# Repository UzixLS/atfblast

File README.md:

## ATFBlast/U

ATF16V8, GAL16V8, ATF22V10 and GAL22V10 chips programmer.

This is custom PCB variant of ATFBlast project.

See http://www.bhabbott.net.nz/atfblast.html for details.

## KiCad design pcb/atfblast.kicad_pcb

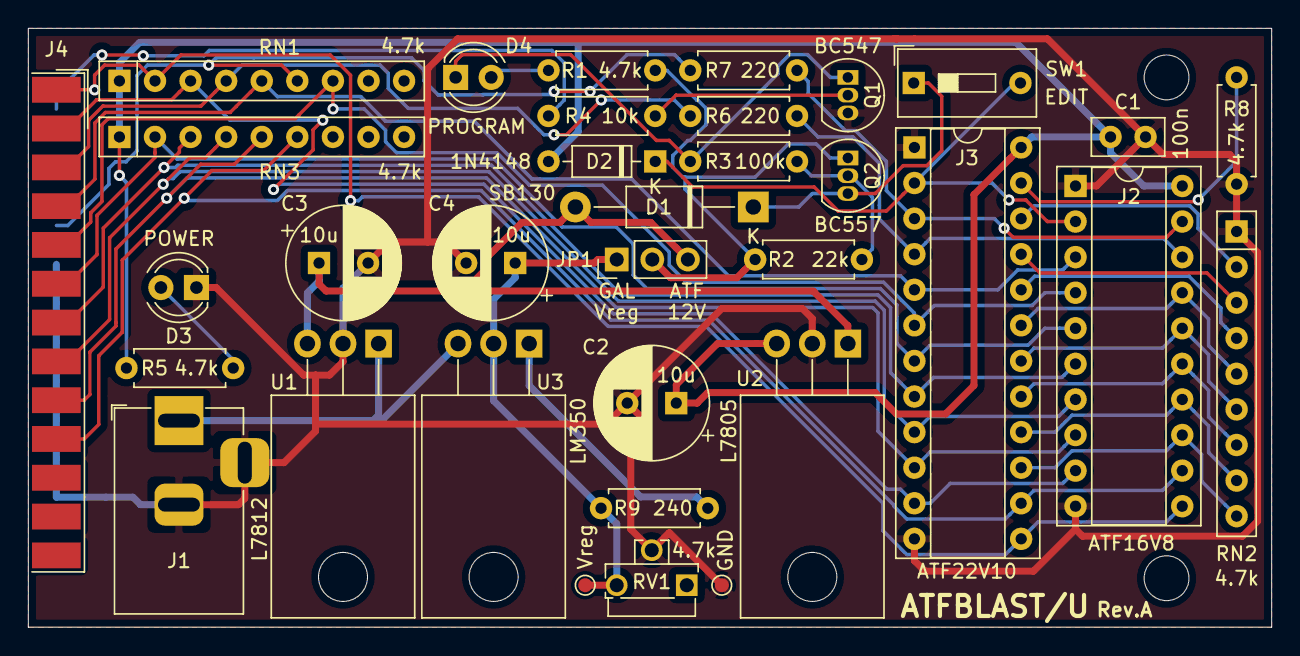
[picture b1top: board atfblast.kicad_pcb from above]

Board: 2 copper layers, 88.8 x 42.8 mm, 36 parts (0 on the bottom side), 37 nets.

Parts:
C1: 100n; C_Disc_D5.0mm_W2.5mm_P2.50mm
C2, C3, C4: 10u; CP_Radial_D8.0mm_P3.50mm
D1: SB130; D_DO-41_SOD81_P12.70mm_Horizontal
D2: 1N4148; D_DO-35_SOD27_P7.62mm_Horizontal
D3, D4: LED; LED_D4.0mm
H1, H2: MountingHole; MountingHole_3.2mm_M3
J1: DS-210; BarrelJack_Horizontal
J2: DIP20-panel; DIP-20_W7.62mm_Socket
J3: DIP24-panel; DIP-24_W7.62mm_Socket
J4: DB25_Male; DSUB-25_Male_EdgeMount_P2.77mm
JP1: Jumper_3; PinHeader_1x03_P2.54mm_Vertical
Q1: BC547; TO-92_Inline
Q2: BC557; TO-92_Inline
R1, R5, R8: 4.7k; R_Axial_DIN0207_L6.3mm_D2.5mm_P7.62mm_Horizontal
R2: 22k; R_Axial_DIN0207_L6.3mm_D2.5mm_P7.62mm_Horizontal
R3: 100k; R_Axial_DIN0207_L6.3mm_D2.5mm_P7.62mm_Horizontal
R4: 10k; R_Axial_DIN0207_L6.3mm_D2.5mm_P7.62mm_Horizontal
R6, R7: 220; R_Axial_DIN0207_L6.3mm_D2.5mm_P7.62mm_Horizontal
R9: 240; R_Axial_DIN0207_L6.3mm_D2.5mm_P7.62mm_Horizontal
RN1, RN2, RN3: 4.7k; R_Array_SIP9
RV1: 4.7k; Potentiometer_Runtron_RM-063_Horizontal
SW1: SW_DIP_x01; SW_DIP_SPSTx01_Slide_9.78x4.72mm_W7.62mm_P2.54mm
TP1: Vreg; TestPoint_Pad_D1.0mm
TP2: GND; TestPoint_Pad_D1.0mm
U1: L7812; TO-220-3_Horizontal_TabDown
U2: L7805; TO-220-3_Horizontal_TabDown
U3: LM350; TO-220-3_Horizontal_TabDown

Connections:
+5V: C1.1, C2.1, D2.2, J2.20, J3.24, R5.1, RN1.1, RN3.1, U2.3
+12V: C3.1, D1.2, JP1.3, U1.3, U2.1
/ACK: J2.12, J3.14, J4.10, RN3.6
/AUTO: J4.14, R4.2
/D0: J2.9, J3.11, J4.2, RN1.3
/D1: J4.3, R6.2, RN1.4
/D2: J2.3, J3.5, J4.4, RN1.5
/D3: J2.4, J3.6, J4.5, RN1.7
/D4: J2.5, J3.7, J4.6, RN3.2
/D5: J2.6, J3.8, J4.7, RN3.3
/D6: J2.7, J3.9, J4.8, RN3.4
/D7: J2.8, J3.10, J4.9, RN3.5
/EDIT: D2.1, J2.2, J3.2, SW1.2
/P_V-: J2.19, J3.3, R7.1
/RA0: J2.18, J3.4, R6.1
/SELECT: J4.17, R7.2, RN1.6
/STROBE: J2.11, J3.13, J4.1, RN1.2
GND: C1.2, C2.2, C3.2, C4.2, D3.1, J1.2, J1.3, J2.1, J2.10, J3.1, J3.12, J4.18, J4.19, J4.20, J4.21, J4.22, J4.23, J4.24, Q1.3, R8.2, RN2.1, RV1.2, TP2.1, U1.2, U2.2
unnamed: C4.1, JP1.1, R9.2, RV1.3, TP1.1, U3.2
unnamed: D1.1, Q2.3, SW1.1
unnamed: D3.2, R5.2
unnamed: D4.1, Q1.1, R3.1
unnamed: D4.2, R1.2
unnamed: J1.1, U1.1, U3.3
unnamed: J2.13, J3.15, RN2.9
unnamed: J2.14, J3.16, RN2.8
unnamed: J2.15, J3.17, RN2.7
unnamed: J2.16, J3.18, RN2.6
unnamed: J2.17, J3.19, RN2.5
unnamed: J3.20, RN2.4
unnamed: J3.21, RN2.3
unnamed: J3.22, RN2.2
unnamed: J3.23, R8.1
unnamed: JP1.2, Q2.1, R1.1, R2.2
unnamed: Q1.2, R4.1
unnamed: Q2.2, R2.1, R3.2
unnamed: R9.1, U3.1

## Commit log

2021-04-09 init
2021-04-09 add doc
2021-04-09 add soft
2021-04-09 add pcb rev.A
2021-04-12 add pcb rev.A1
2021-04-12 add readme
2021-04-12 add prodution files for pcb rev.A1
2021-04-12 add photos
2022-06-19 add license
2026-06-17 remove raw=true from README links
